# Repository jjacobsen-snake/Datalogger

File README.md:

# Datalogger
Arduino based datalogger for tractorpullers

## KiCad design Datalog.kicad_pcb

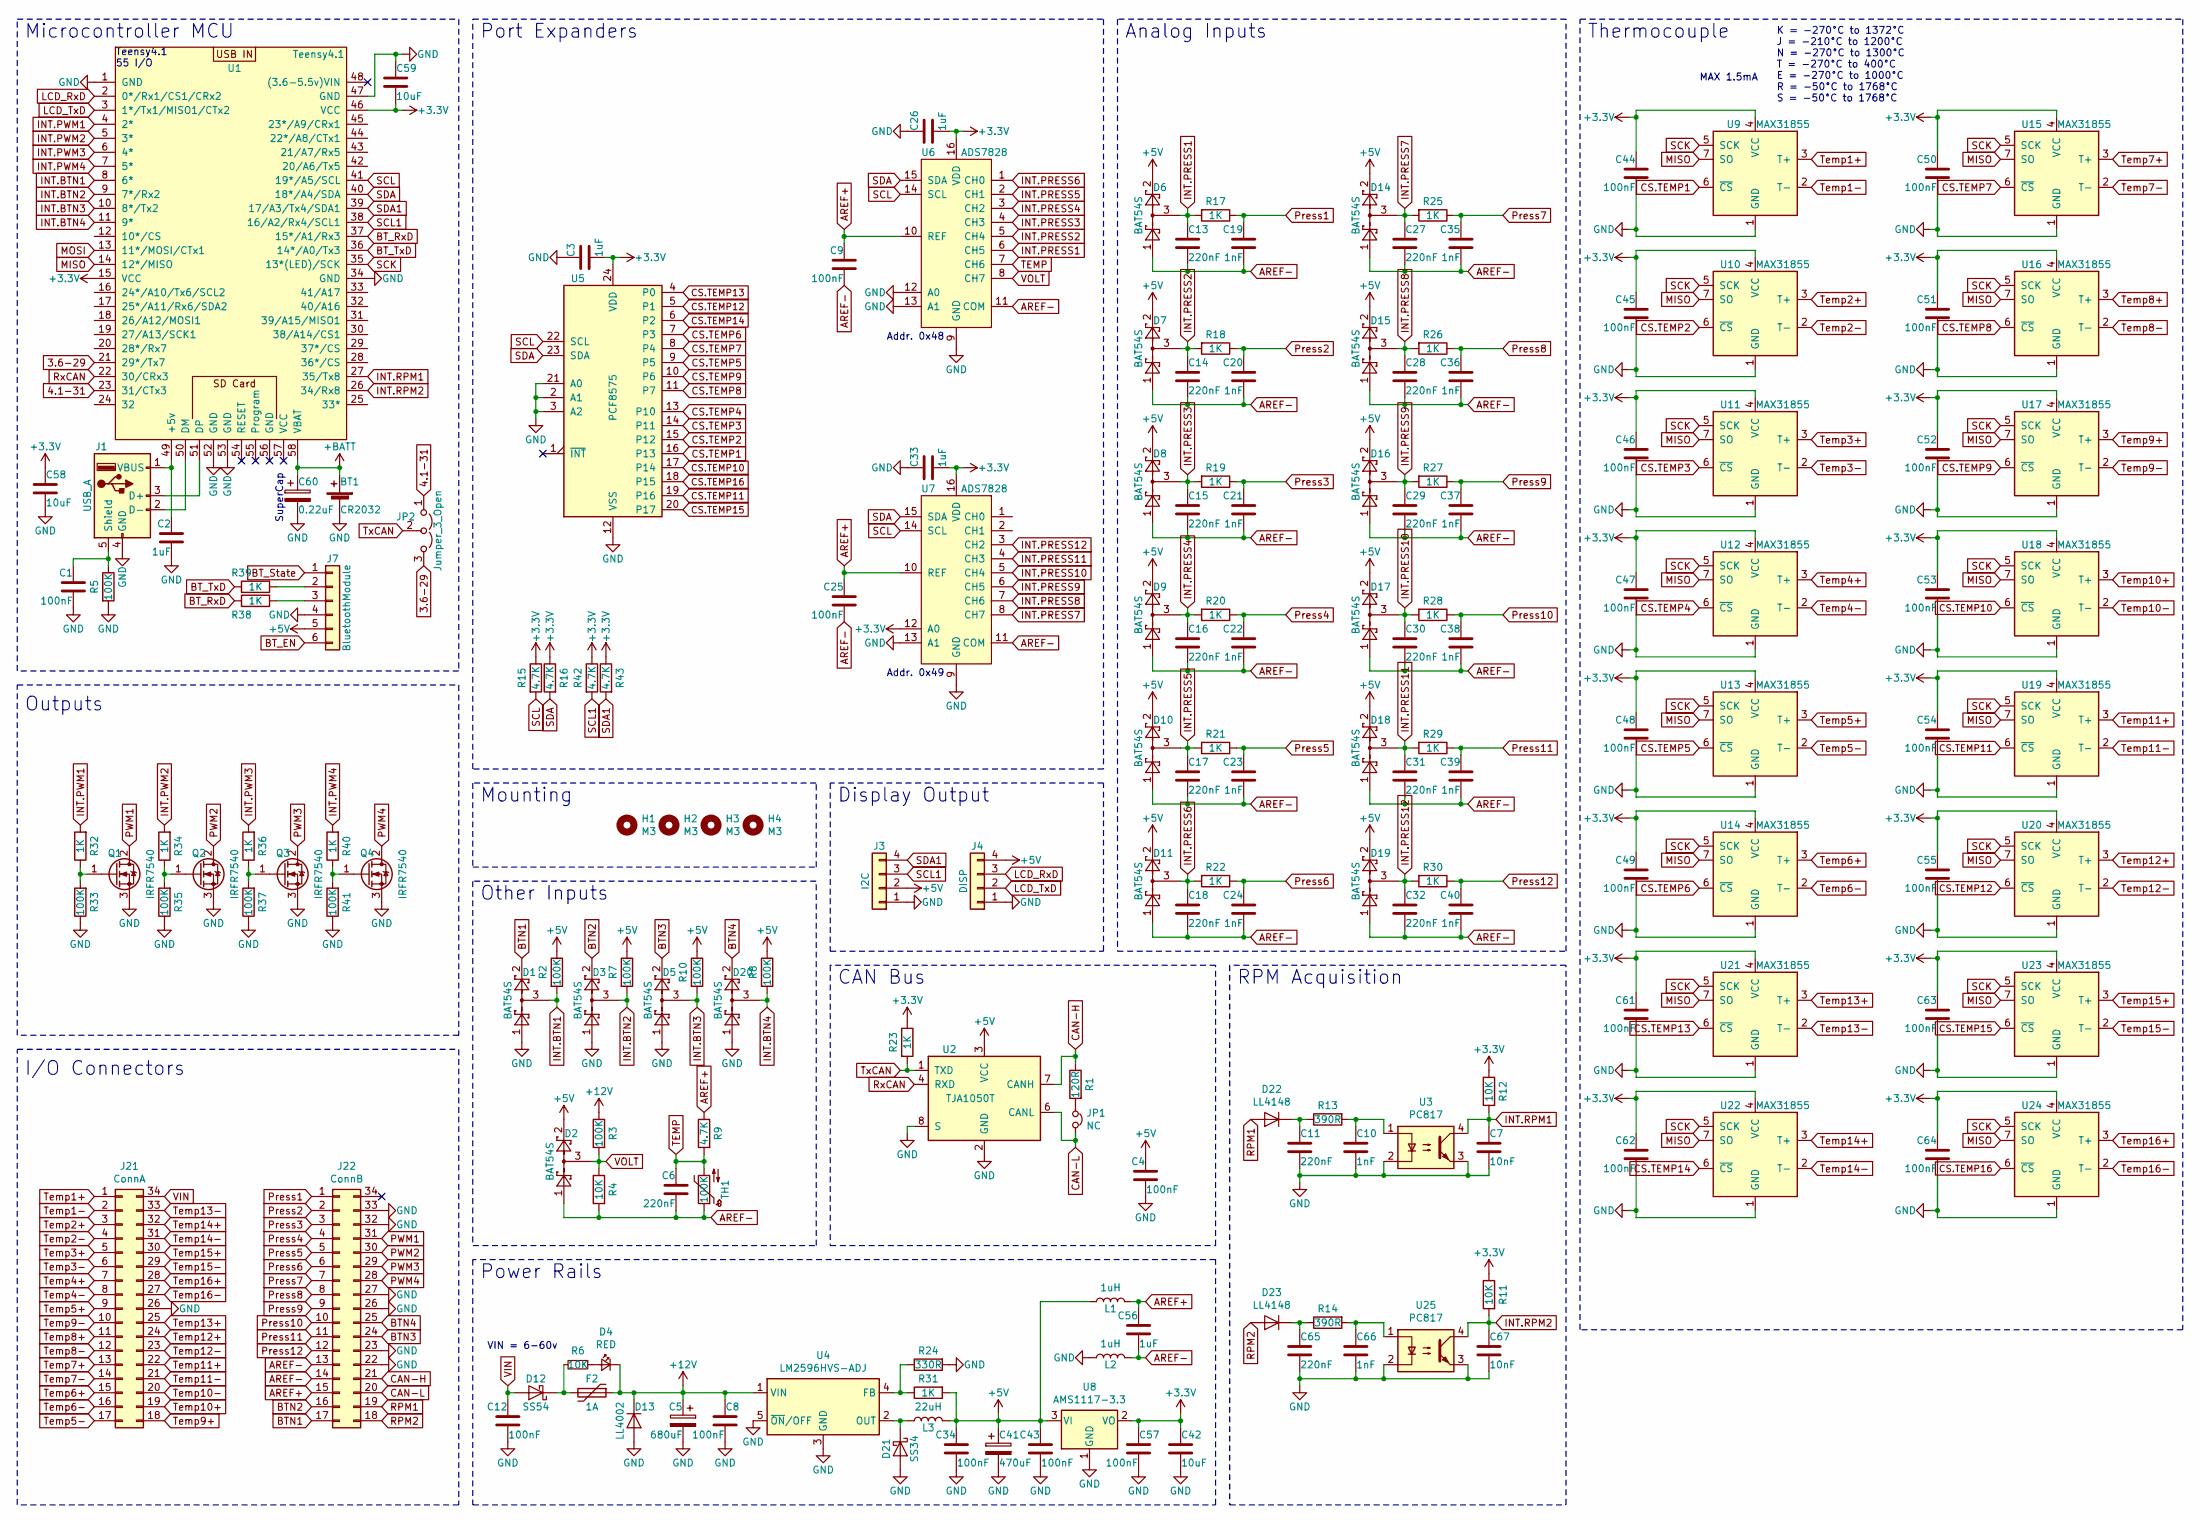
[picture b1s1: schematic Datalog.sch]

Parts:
BT1: CR2032; BatteryHolder_ComfortableElectronic_CH273-2450_1x2450
C1, C4, C9, C25, C44, C45, C46, C47, C48, C49, C50, C51, C52, C53, C54, C55, C61, C62, C63, C64: 100nF; C_0805_2012Metric
C2, C3, C26, C33: 1uF; C_0805_2012Metric
C5: 680uF; CP_Radial_D12.5mm_P5.00mm
C6, C13, C14, C15, C16, C17, C18, C27, C28, C29, C30, C31, C32: 220nF; C_0805_2012Metric
C7, C67: 10nF; C_0805_2012Metric
C8, C12, C34, C43, C57: 100nF; C_1206_3216Metric
C10, C66: 1nF; C_1206_3216Metric
C11, C65: 220nF; C_1206_3216Metric
C19, C20, C21, C22, C23, C24, C35, C36, C37, C38, C39, C40: 1nF; C_0805_2012Metric
C41: 470uF; CP_Radial_D10.0mm_P5.00mm
C42, C58, C59: 10uF; C_1206_3216Metric
C56: 1uF; C_1206_3216Metric
C60: 0.22uF; CP_Radial_D10.0mm_P5.00mm
D1, D2, D3, D5, D6, D7, D8, D9, D10, D11, D14, D15, D16, D17, D18, D19, D20: BAT54S; SOT-23
D4: RED; LED_0805_2012Metric
D12: SS54; D_SMA
D13: LL4002; D_SMA
D21: SS34; D_SMA
D22, D23: LL4148; D_MiniMELF
F2: 1A; Fuse_1206_3216Metric
H1, H2, H3, H4: M3; MountingHole_3.2mm_M3_ISO14580
J1: USB_A; USB_A_Stewart_SS-52100-001_Horizontal
J3: I2C; JST_XH_B4B-XH-A_1x04_P2.50mm_Vertical
J4: DISP; JST_XH_B4B-XH-A_1x04_P2.50mm_Vertical
J7: BluetoothModule; PinSocket_1x06_P2.54mm_Horizontal
J21: ConnA; TE_4-1437290-x
J22: ConnB; TE_4-1437290-x
JP1: NC; SolderJumper-2_P1.3mm_Bridged2Bar_RoundedPad1.0x1.5mm
JP2: Jumper_3_Open; SolderJumper-3_P1.3mm_Open_RoundedPad1.0x1.5mm_NumberLabels
L1, L2: 1uH; L_1206_3216Metric
L3: 22uH; L_12x12mm_H8mm
Q1, Q2, Q3, Q4: IRFR7540; TO-252-2
R1: 120R; R_1206_3216Metric
R2, R3, R5, R7, R8, R10, R33, R35, R37, R41: 100K; R_0805_2012Metric
R4, R6, R11, R12: 10K; R_0805_2012Metric
R9, R15, R16, R42, R43: 4.7K; R_0805_2012Metric
R13, R14: 390R; R_1206_3216Metric
R17, R18, R19, R20, R21, R22, R23, R25, R26, R27, R28, R29, R30, R32, R34, R36, R38, R39, R40: 1K; R_0805_2012Metric
R24: 330R; R_1206_3216Metric
R31: 1K; R_1206_3216Metric
TH1: 100K; R_0805_2012Metric
U1: Teensy4.1; Teensy4.0
U2: TJA1050T; SOIC-8_3.9x4.9mm_P1.27mm
U3, U25: PC817; DIP-4_W7.62mm
U4: LM2596HVS-ADJ; TO-263-5_TabPin3
U5: PCF8575; SOIC-24W_7.5x15.4mm_P1.27mm
U6, U7: ADS7828; TSSOP-16_4.4x5mm_P0.65mm
U8: AMS1117-3.3; SOT-223-3_TabPin2
U9, U10, U11, U12, U13, U14, U15, U16, U17, U18, U19, U20, U21, U22, U23, U24: MAX31855; SOIC-8_3.9x4.9mm_P1.27mm

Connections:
3.6-29: JP2.3 (B), U1.21 (29*/Tx7)
4.1-31: JP2.1 (A), U1.23 (31/CTx3)
+3V3: C3.2, C26.2, C33.2, C42.1, C44.1, C45.1, C46.1, C47.1, C48.1, C49.1, C50.1, C51.1, C52.1, C53.1, C54.1, C55.1, C57.1, C58.1, C59.2, C61.1, C62.1, C63.1, C64.1, R11.1, R12.1, R15.1, R16.1, R23.1, R42.1, R43.1, U1.15 (VCC), U1.46 (VCC), U5.24 (VDD), U6.16 (VDD), U7.12 (A0), U7.16 (VDD), U8.2 (VO), U9.4 (VCC), U10.4 (VCC), U11.4 (VCC), U12.4 (VCC), U13.4 (VCC), U14.4 (VCC), U15.4 (VCC), U16.4 (VCC), U17.4 (VCC), U18.4 (VCC), U19.4 (VCC), U20.4 (VCC), U21.4 (VCC), U22.4 (VCC), U23.4 (VCC), U24.4 (VCC)
+5V: C4.1, C34.1, C41.1, C43.1, D2.2, D6.2, D7.2, D8.2, D9.2, D10.2, D11.2, D14.2, D15.2, D16.2, D17.2, D18.2, D19.2, J3.2, J4.4, J7.5, L1.1, L3.2, R2.1, R7.1, R8.1, R10.1, R31.2, U2.3 (VCC), U8.3 (VI)
+12V: C5.1, C8.1, D4.1 (K), D13.1 (K), F2.1, R3.1, U4.1 (VIN)
+BATT: BT1.1 (+), C60.1, U1.58 (VBAT)
AREF+: C9.1, C25.1, C56.1, J22.15, L1.2, R9.1, U6.10 (REF), U7.10 (REF)
AREF-: C6.2, C9.2, C13.2, C14.2, C15.2, C16.2, C17.2, C18.2, C19.2, C20.2, C21.2, C22.2, C23.2, C24.2, C25.2, C27.2, C28.2, C29.2, C30.2, C31.2, C32.2, C35.2, C36.2, C37.2, C38.2, C39.2, C40.2, C56.2, D2.1, D6.1, D7.1, D8.1, D9.1, D10.1, D11.1, D14.1, D15.1, D16.1, D17.1, D18.1, D19.1, J22.13, J22.14, L2.2, R4.2, TH1.1, U6.11 (COM), U7.11 (COM)
BTN1: D1.2, J22.17
BTN2: D3.2, J22.16
BTN3: D5.2, J22.24
BTN4: D20.2, J22.25
BT_EN: J7.6
BT_RxD: R38.2, U1.37 (15*/A1/Rx3)
BT_State: J7.1
BT_TxD: R39.2, U1.36 (14*/A0/Tx3)
CAN-H: J22.21, R1.1, U2.7 (CANH)
CAN-L: J22.20, JP1.2, U2.6 (CANL)
CS.TEMP1: U5.16 (P13), U9.6 (~CS~)
CS.TEMP2: U5.15 (P12), U10.6 (~CS~)
CS.TEMP3: U5.14 (P11), U11.6 (~CS~)
CS.TEMP4: U5.13 (P10), U12.6 (~CS~)
CS.TEMP5: U5.9 (P5), U13.6 (~CS~)
CS.TEMP6: U5.7 (P3), U14.6 (~CS~)
CS.TEMP7: U5.8 (P4), U15.6 (~CS~)
CS.TEMP8: U5.11 (P7), U16.6 (~CS~)
CS.TEMP9: U5.10 (P6), U17.6 (~CS~)
CS.TEMP10: U5.17 (P14), U18.6 (~CS~)
CS.TEMP11: U5.19 (P16), U19.6 (~CS~)
CS.TEMP12: U5.5 (P1), U20.6 (~CS~)
CS.TEMP13: U5.4 (P0), U21.6 (~CS~)
CS.TEMP14: U5.6 (P2), U22.6 (~CS~)
CS.TEMP15: U5.20 (P17), U23.6 (~CS~)
CS.TEMP16: U5.18 (P15), U24.6 (~CS~)
GND: BT1.2 (-), C1.2, C2.2, C3.1, C4.2, C5.2, C7.2, C8.2, C10.2, C11.2, C12.2, C26.1, C33.1, C34.2, C41.2, C42.2, C43.2, C44.2, C45.2, C46.2, C47.2, C48.2, C49.2, C50.2, C51.2, C52.2, C53.2, C54.2, C55.2, C57.2, C58.2, C59.1, C60.2, C61.2, C62.2, C63.2, C64.2, C65.2, C66.2, C67.2, D1.1, D3.1, D5.1, D13.2 (A), D20.1, D21.2 (A), J1.4 (GND), J3.1, J4.1, J7.4, J21.26, J22.22, J22.23, J22.26, J22.27, J22.32, J22.33, L2.1, Q1.3 (S), Q2.3 (S), Q3.3 (S), Q4.3 (S), R5.2, R24.2, R33.1, R35.1, R37.1, R41.1, U1.1 (GND), U1.34 (GND), U1.47 (GND), U1.52 (GND), U1.53 (GND), U2.2 (GND), U2.8 (S), U3.2, U3.3, U4.3 (GND), U4.5 (~ON~/OFF), U5.2 (A1), U5.3 (A2), U5.12 (VSS), U5.21 (A0), U6.9 (GND), U6.12 (A0), U6.13 (A1), U7.9 (GND), U7.13 (A1), U8.1 (GND), U9.1 (GND), U10.1 (GND), U11.1 (GND), U12.1 (GND), U13.1 (GND), U14.1 (GND), U15.1 (GND), U16.1 (GND), U17.1 (GND), U18.1 (GND), U19.1 (GND), U20.1 (GND), U21.1 (GND), U22.1 (GND), U23.1 (GND), U24.1 (GND), U25.2, U25.3
INT.BTN1: D1.3, R2.2, U1.8 (6*)
INT.BTN2: D3.3, R7.2, U1.9 (7*/Rx2)
INT.BTN3: D5.3, R10.2, U1.10 (8*/Tx2)
INT.BTN4: D20.3, R8.2, U1.11 (9*)
INT.PRESS1: C13.1, D6.3, R17.2, U6.6 (CH5)
INT.PRESS2: C14.1, D7.3, R18.2, U6.5 (CH4)
INT.PRESS3: C15.1, D8.3, R19.2, U6.4 (CH3)
INT.PRESS4: C16.1, D9.3, R20.2, U6.3 (CH2)
INT.PRESS5: C17.1, D10.3, R21.2, U6.2 (CH1)
INT.PRESS6: C18.1, D11.3, R22.2, U6.1 (CH0)
INT.PRESS7: C27.1, D14.3, R25.2, U7.8 (CH7)
INT.PRESS8: C28.1, D15.3, R26.2, U7.7 (CH6)
INT.PRESS9: C29.1, D16.3, R27.2, U7.6 (CH5)
INT.PRESS10: C30.1, D17.3, R28.2, U7.5 (CH4)
INT.PRESS11: C31.1, D18.3, R29.2, U7.4 (CH3)
INT.PRESS12: C32.1, D19.3, R30.2, U7.3 (CH2)
INT.PWM1: R32.2, U1.4 (2*)
INT.PWM2: R34.2, U1.5 (3*)
INT.PWM3: R36.2, U1.6 (4*)
INT.PWM4: R40.2, U1.7 (5*)
INT.RPM1: C7.1, R12.2, U1.27 (35/Tx8), U3.4
INT.RPM2: C67.1, R11.2, U1.26 (34/Rx8), U25.4
LCD_RxD: J4.3, U1.2 (0*/Rx1/CS1/CRx2)
LCD_TxD: J4.2, U1.3 (1*/Tx1/MISO1/CTx2)
MISO: U1.14 (12*/MISO), U9.7 (SO), U10.7 (SO), U11.7 (SO), U12.7 (SO), U13.7 (SO), U14.7 (SO), U15.7 (SO), U16.7 (SO), U17.7 (SO), U18.7 (SO), U19.7 (SO), U20.7 (SO), U21.7 (SO), U22.7 (SO), U23.7 (SO), U24.7 (SO)
MOSI: U1.13 (11*/MOSI/CTx1)
unnamed: C1.1, J1.5 (Shield), R5.1
unnamed: C2.1, J1.1 (VBUS), U1.49 (+5v)
unnamed: C10.1, R13.2, U3.1
unnamed: C11.1, D22.1 (K), R13.1
unnamed: C65.1, D23.1 (K), R14.1
unnamed: C66.1, R14.2, U25.1
unnamed: D4.2 (A), R6.1
unnamed: D12.1 (K), F2.2, R6.2
unnamed: D21.1 (K), L3.1, U4.2 (OUT)
unnamed: J1.2 (D-), U1.50 (DM)
unnamed: J1.3 (D+), U1.51 (DP)
unnamed: J7.2, R39.1
unnamed: J7.3, R38.1
unnamed: JP1.1, R1.2
unnamed: Q1.1 (G), R32.1, R33.2
unnamed: Q2.1 (G), R34.1, R35.2
unnamed: Q3.1 (G), R36.1, R37.2
unnamed: Q4.1 (G), R40.1, R41.2
unnamed: R24.1, R31.1, U4.4 (FB)
PWM1: J22.31, Q1.2 (D)
PWM2: J22.30, Q2.2 (D)
PWM3: J22.29, Q3.2 (D)
PWM4: J22.28, Q4.2 (D)
Press1: C19.1, J22.1, R17.1
Press2: C20.1, J22.2, R18.1
Press3: C21.1, J22.3, R19.1
Press4: C22.1, J22.4, R20.1
Press5: C23.1, J22.5, R21.1
Press6: C24.1, J22.6, R22.1
Press7: C35.1, J22.7, R25.1
Press8: C36.1, J22.8, R26.1
Press9: C37.1, J22.9, R27.1
Press10: C38.1, J22.10, R28.1
Press11: C39.1, J22.11, R29.1
Press12: C40.1, J22.12, R30.1
RPM1: D22.2 (A), J22.19
RPM2: D23.2 (A), J22.18
RxCAN: U1.22 (30/CRx3), U2.4 (RXD)
SCK: U1.35 (13*(LED)/SCK), U9.5 (SCK), U10.5 (SCK), U11.5 (SCK), U12.5 (SCK), U13.5 (SCK), U14.5 (SCK), U15.5 (SCK), U16.5 (SCK), U17.5 (SCK), U18.5 (SCK), U19.5 (SCK), U20.5 (SCK), U21.5 (SCK), U22.5 (SCK), U23.5 (SCK), U24.5 (SCK)
SCL: R15.2, U1.41 (19*/A5/SCL), U5.22 (SCL), U6.14 (SCL), U7.14 (SCL)
SCL1: J3.3, R42.2, U1.38 (16/A2/Rx4/SCL1)
SDA: R16.2, U1.40 (18*/A4/SDA), U5.23 (SDA), U6.15 (SDA), U7.15 (SDA)
SDA1: J3.4, R43.2, U1.39 (17/A3/Tx4/SDA1)
TEMP: C6.1, R9.2, TH1.2, U6.7 (CH6)
Temp1+: J21.1, U9.3 (T+)
Temp1-: J21.2, U9.2 (T-)
Temp2+: J21.3, U10.3 (T+)
Temp2-: J21.4, U10.2 (T-)
Temp3+: J21.5, U11.3 (T+)
Temp3-: J21.6, U11.2 (T-)
Temp4+: J21.7, U12.3 (T+)
Temp4-: J21.8, U12.2 (T-)
Temp5+: J21.9, U13.3 (T+)
Temp5-: J21.17, U13.2 (T-)
Temp6+: J21.15, U14.3 (T+)
Temp6-: J21.16, U14.2 (T-)
Temp7+: J21.13, U15.3 (T+)
Temp7-: J21.14, U15.2 (T-)
Temp8+: J21.11, U16.3 (T+)
Temp8-: J21.12, U16.2 (T-)
Temp9+: J21.18, U17.3 (T+)
Temp9-: J21.10, U17.2 (T-)
Temp10+: J21.19, U18.3 (T+)
Temp10-: J21.20, U18.2 (T-)
Temp11+: J21.22, U19.3 (T+)
Temp11-: J21.21, U19.2 (T-)
Temp12+: J21.24, U20.3 (T+)
Temp12-: J21.23, U20.2 (T-)
Temp13+: J21.25, U21.3 (T+)
Temp13-: J21.33, U21.2 (T-)
Temp14+: J21.32, U22.3 (T+)
Temp14-: J21.31, U22.2 (T-)
Temp15+: J21.30, U23.3 (T+)
Temp15-: J21.29, U23.2 (T-)
Temp16+: J21.28, U24.3 (T+)
Temp16-: J21.27, U24.2 (T-)
TxCAN: JP2.2 (C), R23.2, U2.1 (TXD)
VIN: C12.1, D12.2 (A), J21.34
VOLT: D2.3, R3.2, R4.1, U6.8 (CH7)

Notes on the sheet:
K = -270°C to 1372°C J = -210°C to 1200°C N = -270°C to 1300°C T = -270°C to 400°C E = -270°C to 1000°C R = -50°C to 1768°C S = -50°C to 1768°C
Thermocouple
Analog Inputs
Port Expanders
Power Rails
RPM Acquisition
Display Output
Other Inputs
CAN Bus
Teensy4.1 55 I/O
VIN = 6-60v
Microcontroller MCU
MAX 1.5mA
I/O Connectors
Mounting
Addr. 0x48
Addr. 0x49
SuperCap
Outputs

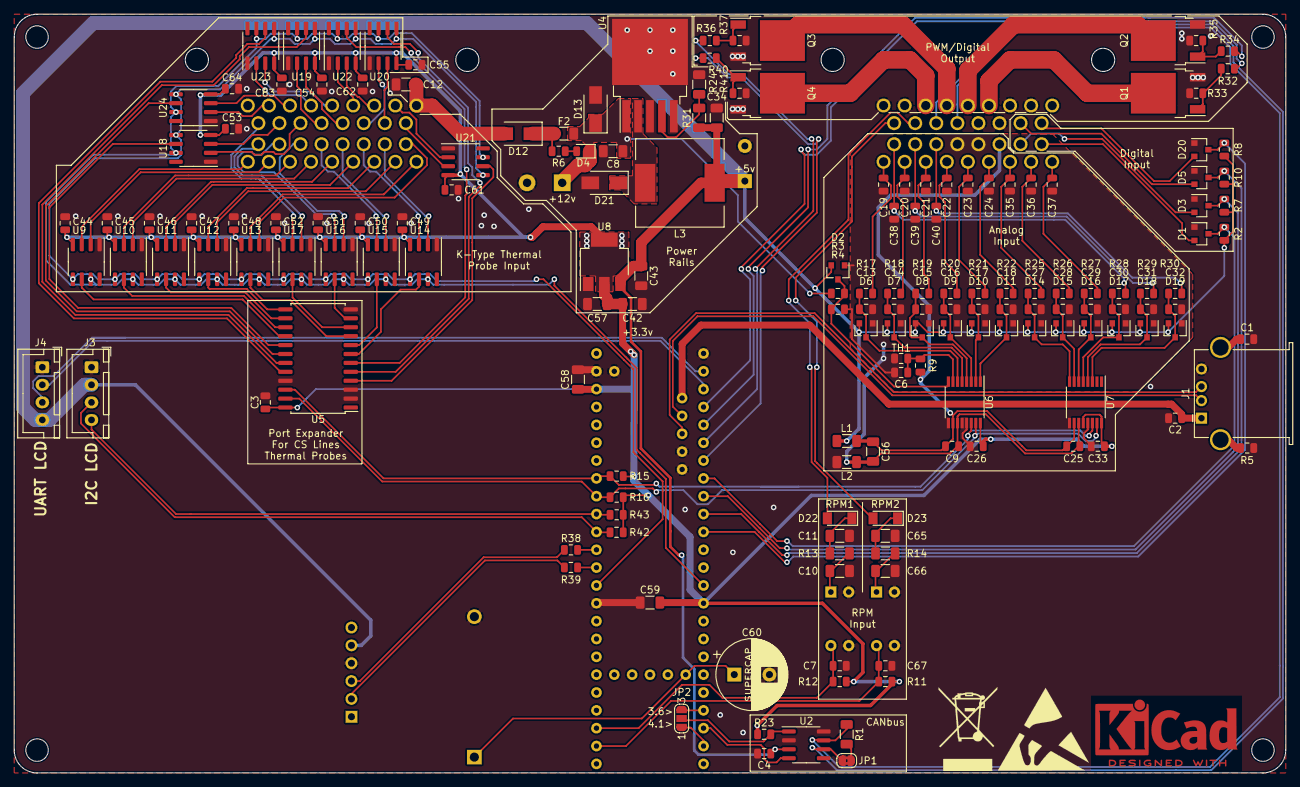
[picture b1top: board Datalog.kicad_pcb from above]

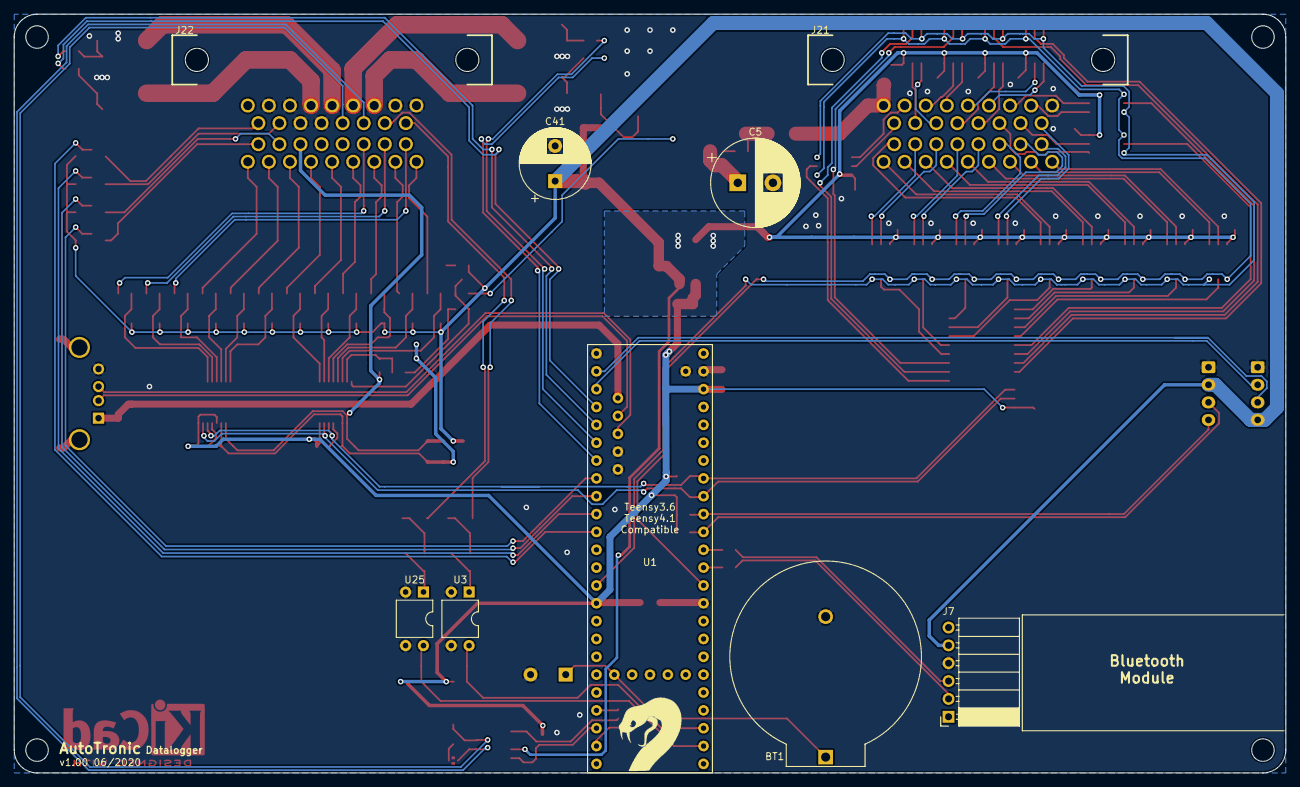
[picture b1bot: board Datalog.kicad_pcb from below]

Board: 2 copper layers, 181.0 x 108.0 mm, 180 parts (9 on the bottom side), 137 nets.
